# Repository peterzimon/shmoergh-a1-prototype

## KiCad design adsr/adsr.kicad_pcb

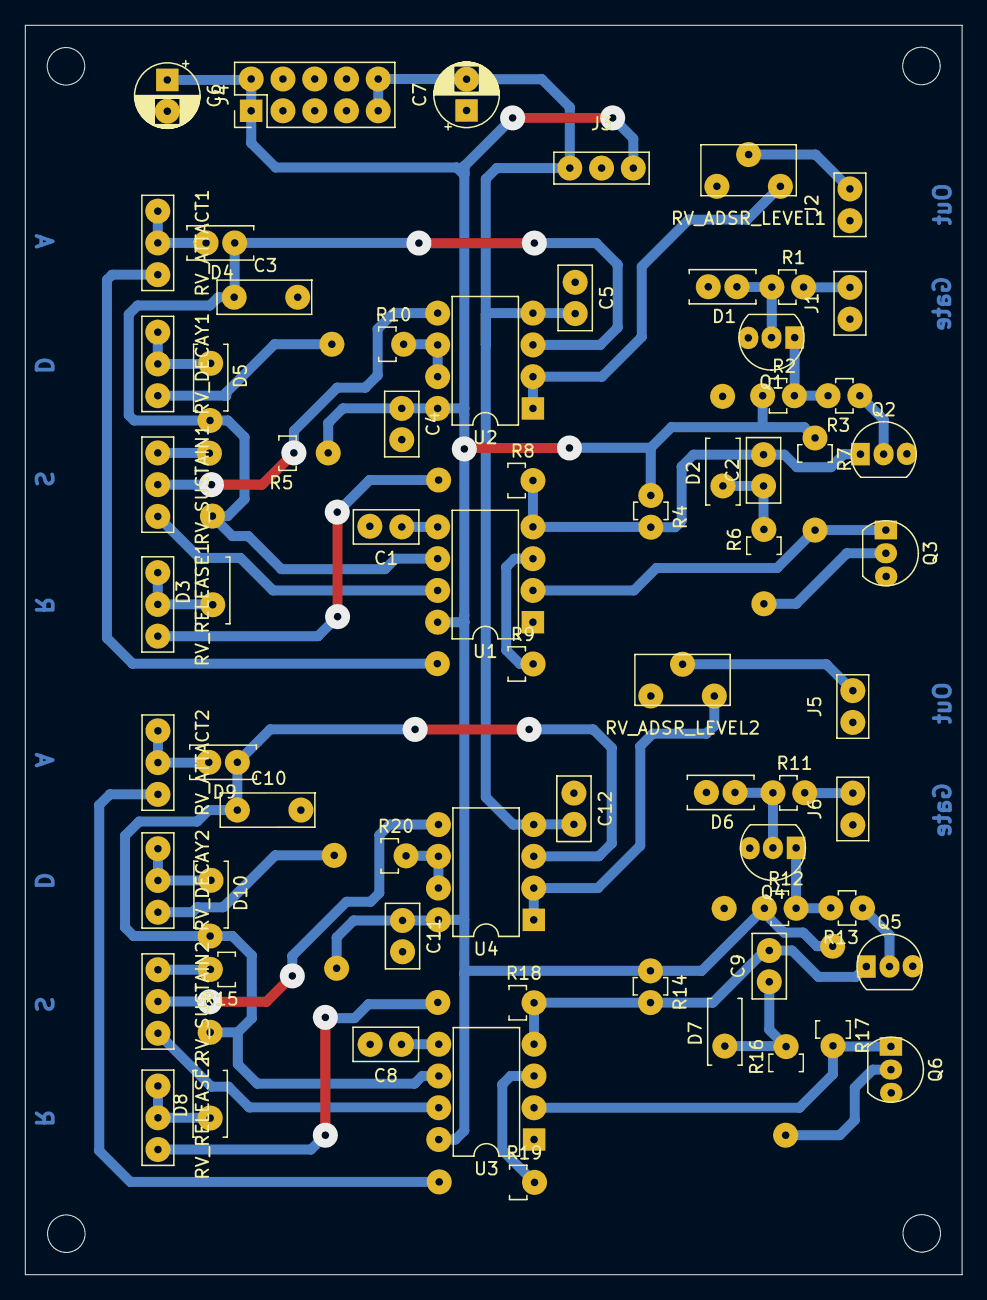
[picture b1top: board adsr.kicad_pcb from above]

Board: 2 copper layers, 74.9 x 99.9 mm, 68 parts (0 on the bottom side), 49 nets.

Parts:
C1, C2, C8, C9: 10n; C_Disc_D5.0mm_W2.5mm_P2.50mm
C3, C10: 2.2u; C_Foil_P5.48mm
C4, C5, C11, C12: 100n; C_Disc_D5.0mm_W2.5mm_P2.50mm
C6, C7: 10u; CP_Radial_D5.0mm_P2.50mm
D1, D2, D3, D4, D5, D6, D7, D8, D9, D10: 1N4148; D_Axial-Vertical
J1, J6: Gate In; NSL25_01x02_Vertical
J2, J5: Out; NSL25_01x02_Vertical
J3: Custom Power; NSL25_01x03_Vertical
J4: Eurorack Power; Eurorack_Power_Supply
Q1, Q2, Q3, Q4, Q5, Q6: BC547; TO-92_Inline
R1, R6, R11, R16: 10k; R_Axial_Vertical
R2, R4, R5, R7, R12, R14, R15, R17: 4.7k; R_Axial_Vertical
R3, R13: 22k; R_Axial_Vertical
R8, R9, R10, R18, R19, R20: 100; R_Axial_Vertical
RV_ADSR_LEVEL1, RV_ADSR_LEVEL2: 1k; TrimPot_Vertical
RV_ATTACT1, RV_ATTACT2: 1M; NSL25_01x03_Vertical
RV_DECAY1, RV_DECAY2: 1M; NSL25_01x03_Vertical
RV_RELEASE1, RV_RELEASE2: 1M; NSL25_01x03_Vertical
RV_SUSTAIN1, RV_SUSTAIN2: 10k; NSL25_01x03_Vertical
U1, U3: 7555; DIP-8_W7.62mm
U2, U4: TL072; DIP-8_W7.62mm

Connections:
+12V: C4.1, C6.1, C11.1, J3.1, J4.1, J4.2, R2.1, R4.1, R5.1, R7.1, R12.1, R14.1, R15.1, R17.1, U1.8, U2.8, U3.8, U4.8
-12V: C5.2, C7.2, C12.2, J3.3, J4.9, J4.10, U2.4, U4.4
/ADSR 1/ADSR_OUT: J2.1, RV_ADSR_LEVEL1.2
/ADSR 1/GATE: J1.1, R1.2
/ADSR 1/RESET: C2.2, Q2.1, R4.2, R8.2, U1.4
/ADSR 1/TRIGGER: Q3.1, R7.2, U1.2
/ADSR 2/ADSR_OUT: J5.1, RV_ADSR_LEVEL2.2
/ADSR 2/GATE: J6.1, R11.2
/ADSR 2/RESET: C9.2, Q5.1, R14.2, R18.2, U3.4
/ADSR 2/TRIGGER: Q6.1, R17.2, U3.2
GND: C1.2, C3.2, C4.2, C5.1, C6.2, C7.1, C8.2, C10.2, C11.2, C12.1, D1.2, D2.2, D6.2, D7.2, J1.2, J2.2, J3.2, J4.3, J4.4, J4.5, J4.6, J4.7, J4.8, J5.2, J6.2, Q1.3, Q2.3, Q3.3, Q4.3, Q5.3, Q6.3, RV_ADSR_LEVEL1.1, RV_ADSR_LEVEL2.1, U1.1, U3.1
unnamed: C1.1, U1.5
unnamed: C2.1, D2.1, R6.2
unnamed: C3.1, D3.2, D4.1, D5.2, U1.6, U2.3
unnamed: C8.1, U3.5
unnamed: C9.1, D7.1, R16.2
unnamed: C10.1, D8.2, D9.1, D10.2, U3.6, U4.3
unnamed: D1.1, Q1.2, R1.1
unnamed: D3.1, RV_RELEASE1.2, RV_RELEASE1.3
unnamed: D4.2, RV_ATTACT1.2, RV_ATTACT1.3
unnamed: D5.1, RV_DECAY1.2, RV_DECAY1.3
unnamed: D6.1, Q4.2, R11.1
unnamed: D8.1, RV_RELEASE2.2, RV_RELEASE2.3
unnamed: D9.2, RV_ATTACT2.2, RV_ATTACT2.3
unnamed: D10.1, RV_DECAY2.2, RV_DECAY2.3
unnamed: Q1.1, R2.2, R3.2
unnamed: Q2.2, R3.1
unnamed: Q3.2, R6.1
unnamed: Q4.1, R12.2, R13.2
unnamed: Q5.2, R13.1
unnamed: Q6.2, R16.1
unnamed: R5.2, RV_SUSTAIN1.3
unnamed: R8.1, RV_RELEASE1.1
unnamed: R9.1, RV_ATTACT1.1
unnamed: R9.2, U1.3
unnamed: R10.1, RV_DECAY1.1
unnamed: R10.2, U2.6, U2.7
unnamed: R15.2, RV_SUSTAIN2.3
unnamed: R18.1, RV_RELEASE2.1
unnamed: R19.1, RV_ATTACT2.1
unnamed: R19.2, U3.3
unnamed: R20.1, RV_DECAY2.1
unnamed: R20.2, U4.6, U4.7
unnamed: RV_ADSR_LEVEL1.3, U2.1, U2.2
unnamed: RV_ADSR_LEVEL2.3, U4.1, U4.2
unnamed: RV_SUSTAIN1.1, U1.7
unnamed: RV_SUSTAIN1.2, U2.5
unnamed: RV_SUSTAIN2.1, U3.7
unnamed: RV_SUSTAIN2.2, U4.5
